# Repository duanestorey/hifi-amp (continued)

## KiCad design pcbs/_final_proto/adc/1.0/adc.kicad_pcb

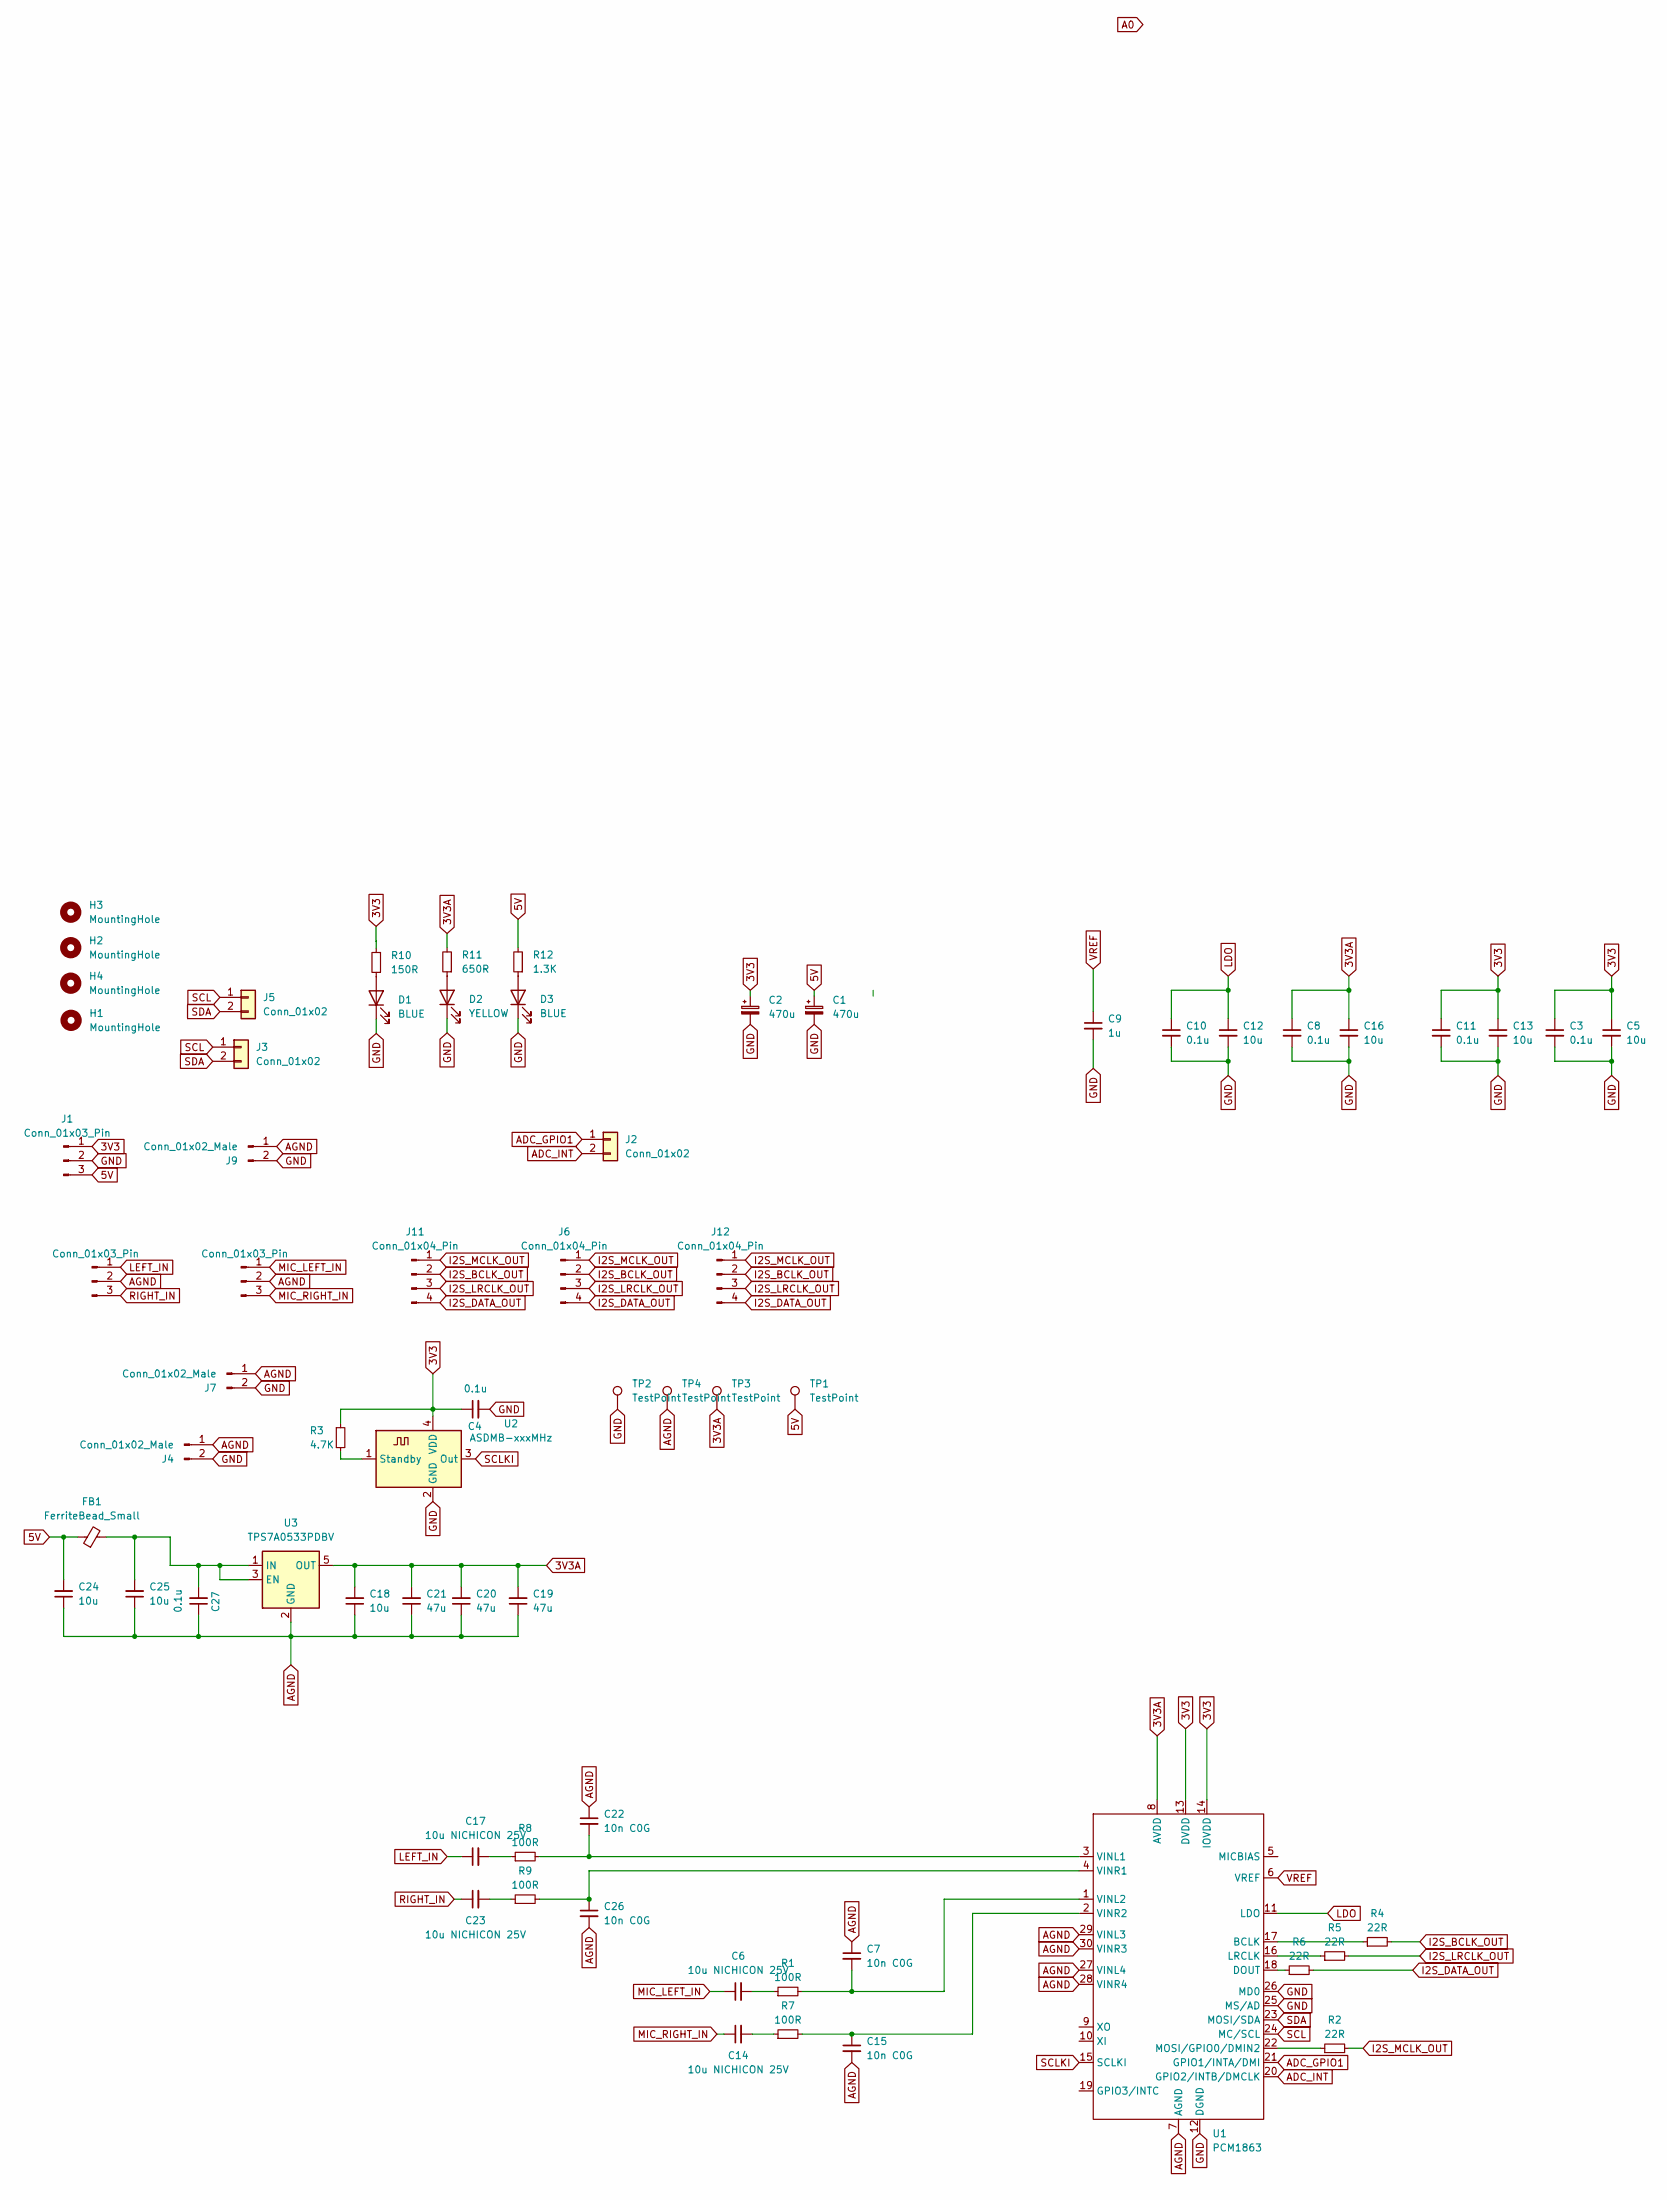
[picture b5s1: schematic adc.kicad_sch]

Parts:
C1, C2: 470u; CP_Radial_D6.3mm_P2.50mm
C3, C8, C10, C11: 0.1u; C_0805_2012Metric_Pad1.18x1.45mm_HandSolder
C4, C27: 0.1u; C_0805_2012Metric_Pad1.18x1.45mm_HandSolder; Mouser 791-0805N103G250CT
C5, C12, C13, C16, C18, C24, C25: 10u; C_1206_3216Metric_Pad1.33x1.80mm_HandSolder
C6, C14, C17, C23: 10u NICHICON 25V; CP_Radial_D5.0mm_P2.00mm
C7, C15, C22, C26: 10n C0G; C_0805_2012Metric_Pad1.18x1.45mm_HandSolder; Mouser 791-0805N103G250CT
C9: 1u; C_1206_3216Metric_Pad1.33x1.80mm_HandSolder
C19, C20, C21: 47u; C_1206_3216Metric_Pad1.33x1.80mm_HandSolder
D1, D3: BLUE; LED_0603_1608Metric
D2: YELLOW; LED_0603_1608Metric
FB1: FerriteBead_Small; R_0603_1608Metric_Pad0.98x0.95mm_HandSolder
H1, H2, H3, H4: MountingHole; MountingHole_3.2mm_M3_DIN965_Pad_TopOnly
J1, J8, J10: Conn_01x03_Pin; JST_PH_B3B-PH-K_1x03_P2.00mm_Vertical
J2, J3, J5: Conn_01x02; JST_PH_B2B-PH-K_1x02_P2.00mm_Vertical
J4, J7, J9: Conn_01x02_Male; PinHeader_1x02_P2.54mm_Vertical
J6, J11: Conn_01x04_Pin; JST_PH_B4B-PH-K_1x04_P2.00mm_Vertical
J12: Conn_01x04_Pin; PinHeader_1x04_P2.54mm_Vertical
R1, R7, R8, R9: 100R; R_0805_2012Metric_Pad1.20x1.40mm_HandSolder; Mouser 603-RT0805FRE13100RL
R2, R4, R5, R6: 22R; R_0805_2012Metric_Pad1.20x1.40mm_HandSolder; Mouser 603-RT0805FRE0722RL
R3: 4.7K; R_0603_1608Metric_Pad0.98x0.95mm_HandSolder; Mouser 603-RT0805FRE0722RL
R10: 150R; R_0603_1608Metric_Pad0.98x0.95mm_HandSolder
R11: 650R; R_0603_1608Metric_Pad0.98x0.95mm_HandSolder
R12: 1.3K; R_0603_1608Metric_Pad0.98x0.95mm_HandSolder
TP1, TP2, TP3, TP4: TestPoint; TestPoint_THTPad_2.5x2.5mm_Drill1.2mm
U1: PCM1863; TSSOP-30_4.4x7.8mm_P0.5mm; Mouser 595-PCM1863DBT
U2: ASDMB-xxxMHz; Oscillator_SMD_Abracon_ASE-4Pin_3.2x2.5mm; Mouser 346-3225Z24.5760C1KX
U3: TPS7A0533PDBV; SOT-23-5

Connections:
3V3: C2.1, C3.1, C4.1, C5.1, C11.1, C13.1, J1.1, R3.1, R10.2, U1.13 (DVDD), U1.14 (IOVDD), U2.4 (VDD)
3V3A: C8.1, C16.1, C18.2, C19.2, C20.2, C21.2, R11.2, TP3.1, U1.8 (AVDD), U3.5 (OUT)
5V: C1.1, C24.2, FB1.1, J1.3, R12.2, TP1.1
ADC_GPIO1: J2.1, U1.21 (GPIO1/INTA/DMI)
ADC_INT: J2.2, U1.20 (GPIO2/INTB/DMCLK)
AGND: C7.1, C15.2, C18.1, C19.1, C20.1, C21.1, C22.1, C24.1, C25.1, C26.2, C27.1, J4.1, J7.1, J8.2, J9.1, J10.2, TP4.1, U1.7 (AGND), U1.27 (VINL4), U1.28 (VINR4), U1.29 (VINL3), U1.30 (VINR3), U3.2 (GND)
GND: C1.2, C2.2, C3.2, C4.2, C5.2, C8.2, C9.2, C10.2, C11.2, C12.2, C13.2, C16.2, D1.1 (K), D2.1 (K), D3.1 (K), J1.2, J4.2, J7.2, J9.2, TP2.1, U1.12 (DGND), U1.25 (MS/AD), U1.26 (MD0), U2.2 (GND)
I2S_BCLK_OUT: J6.2, J11.2, J12.2, R4.2
I2S_DATA_OUT: J6.4, J11.4, J12.4, R6.2
I2S_LRCLK_OUT: J6.3, J11.3, J12.3, R5.2
I2S_MCLK_OUT: J6.1, J11.1, J12.1, R2.2
LDO: C10.1, C12.1, U1.11 (LDO)
LEFT_IN: C17.1, J10.1
MIC_LEFT_IN: C6.1, J8.1
MIC_RIGHT_IN: C14.1, J8.3
unnamed: C6.2, R1.1
unnamed: C14.2, R7.1
unnamed: C17.2, R8.1
unnamed: C23.2, R9.1
unnamed: D1.2 (A), R10.1
unnamed: D2.2 (A), R11.1
unnamed: D3.2 (A), R12.1
unnamed: R4.1, U1.17 (BCLK)
unnamed: R6.1, U1.18 (DOUT)
unnamed: R5.1, U1.16 (LRCLK)
unnamed: R2.1, U1.22 (MOSI/GPIO0/DMIN2)
unnamed: C22.2, R8.2, U1.3 (VINL1)
unnamed: C7.2, R1.2, U1.1 (VINL2)
unnamed: C26.1, R9.2, U1.4 (VINR1)
unnamed: C15.1, R7.2, U1.2 (VINR2)
unnamed: R3.2, U2.1 (Standby)
unnamed: C25.2, C27.2, FB1.2, U3.1 (IN), U3.3 (EN)
RIGHT_IN: C23.1, J10.3
SCL: J3.1, J5.1, U1.24 (MC/SCL)
SCLKI: U1.15 (SCLKI), U2.3 (Out)
SDA: J3.2, J5.2, U1.23 (MOSI/SDA)
VREF: C9.1, U1.6 (VREF)

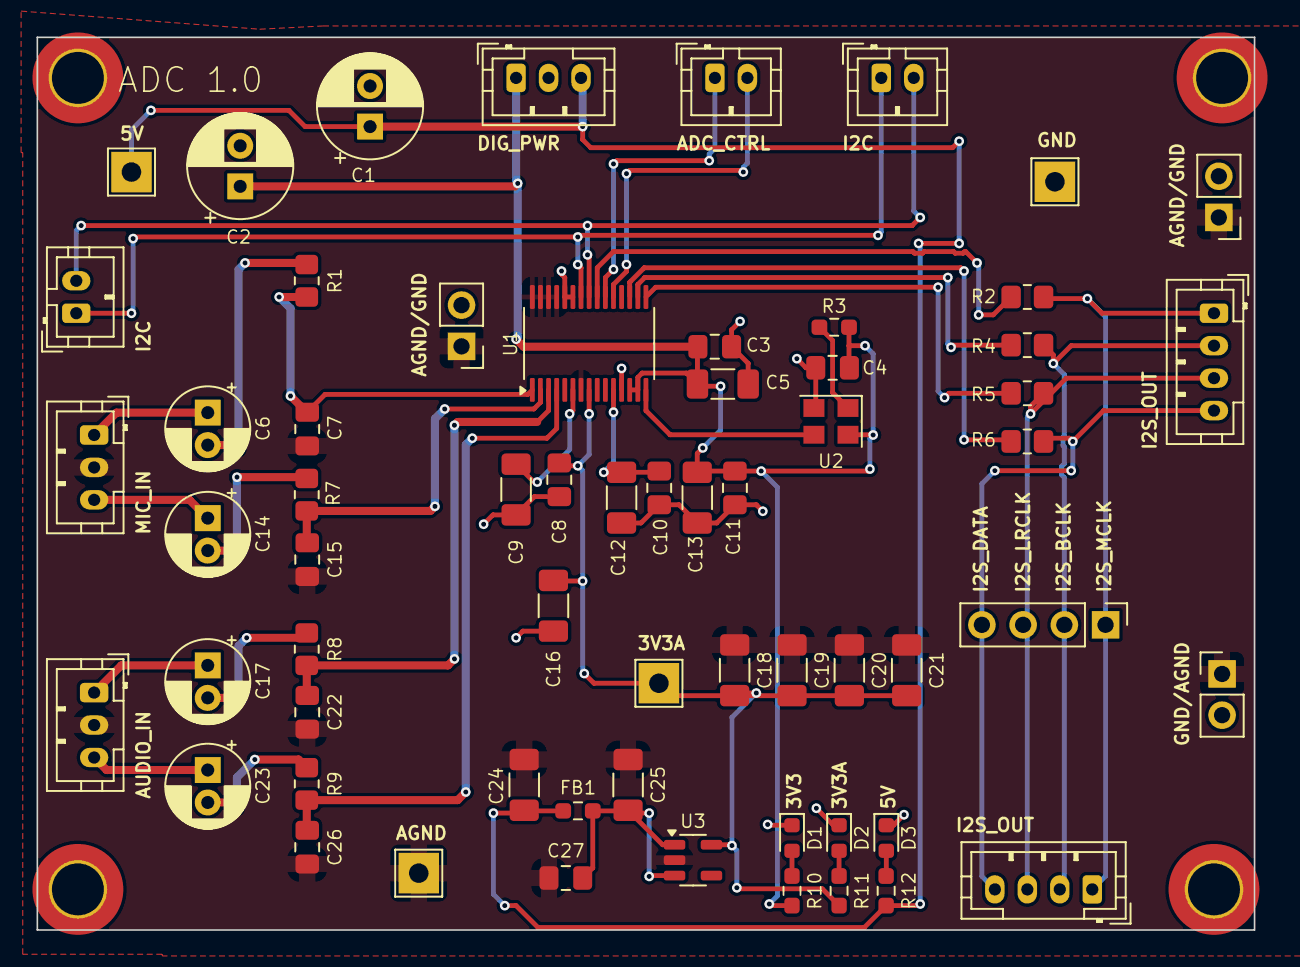
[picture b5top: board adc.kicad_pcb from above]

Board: 2 copper layers, 75.0 x 55.0 mm, 66 parts (0 on the bottom side), 37 nets.

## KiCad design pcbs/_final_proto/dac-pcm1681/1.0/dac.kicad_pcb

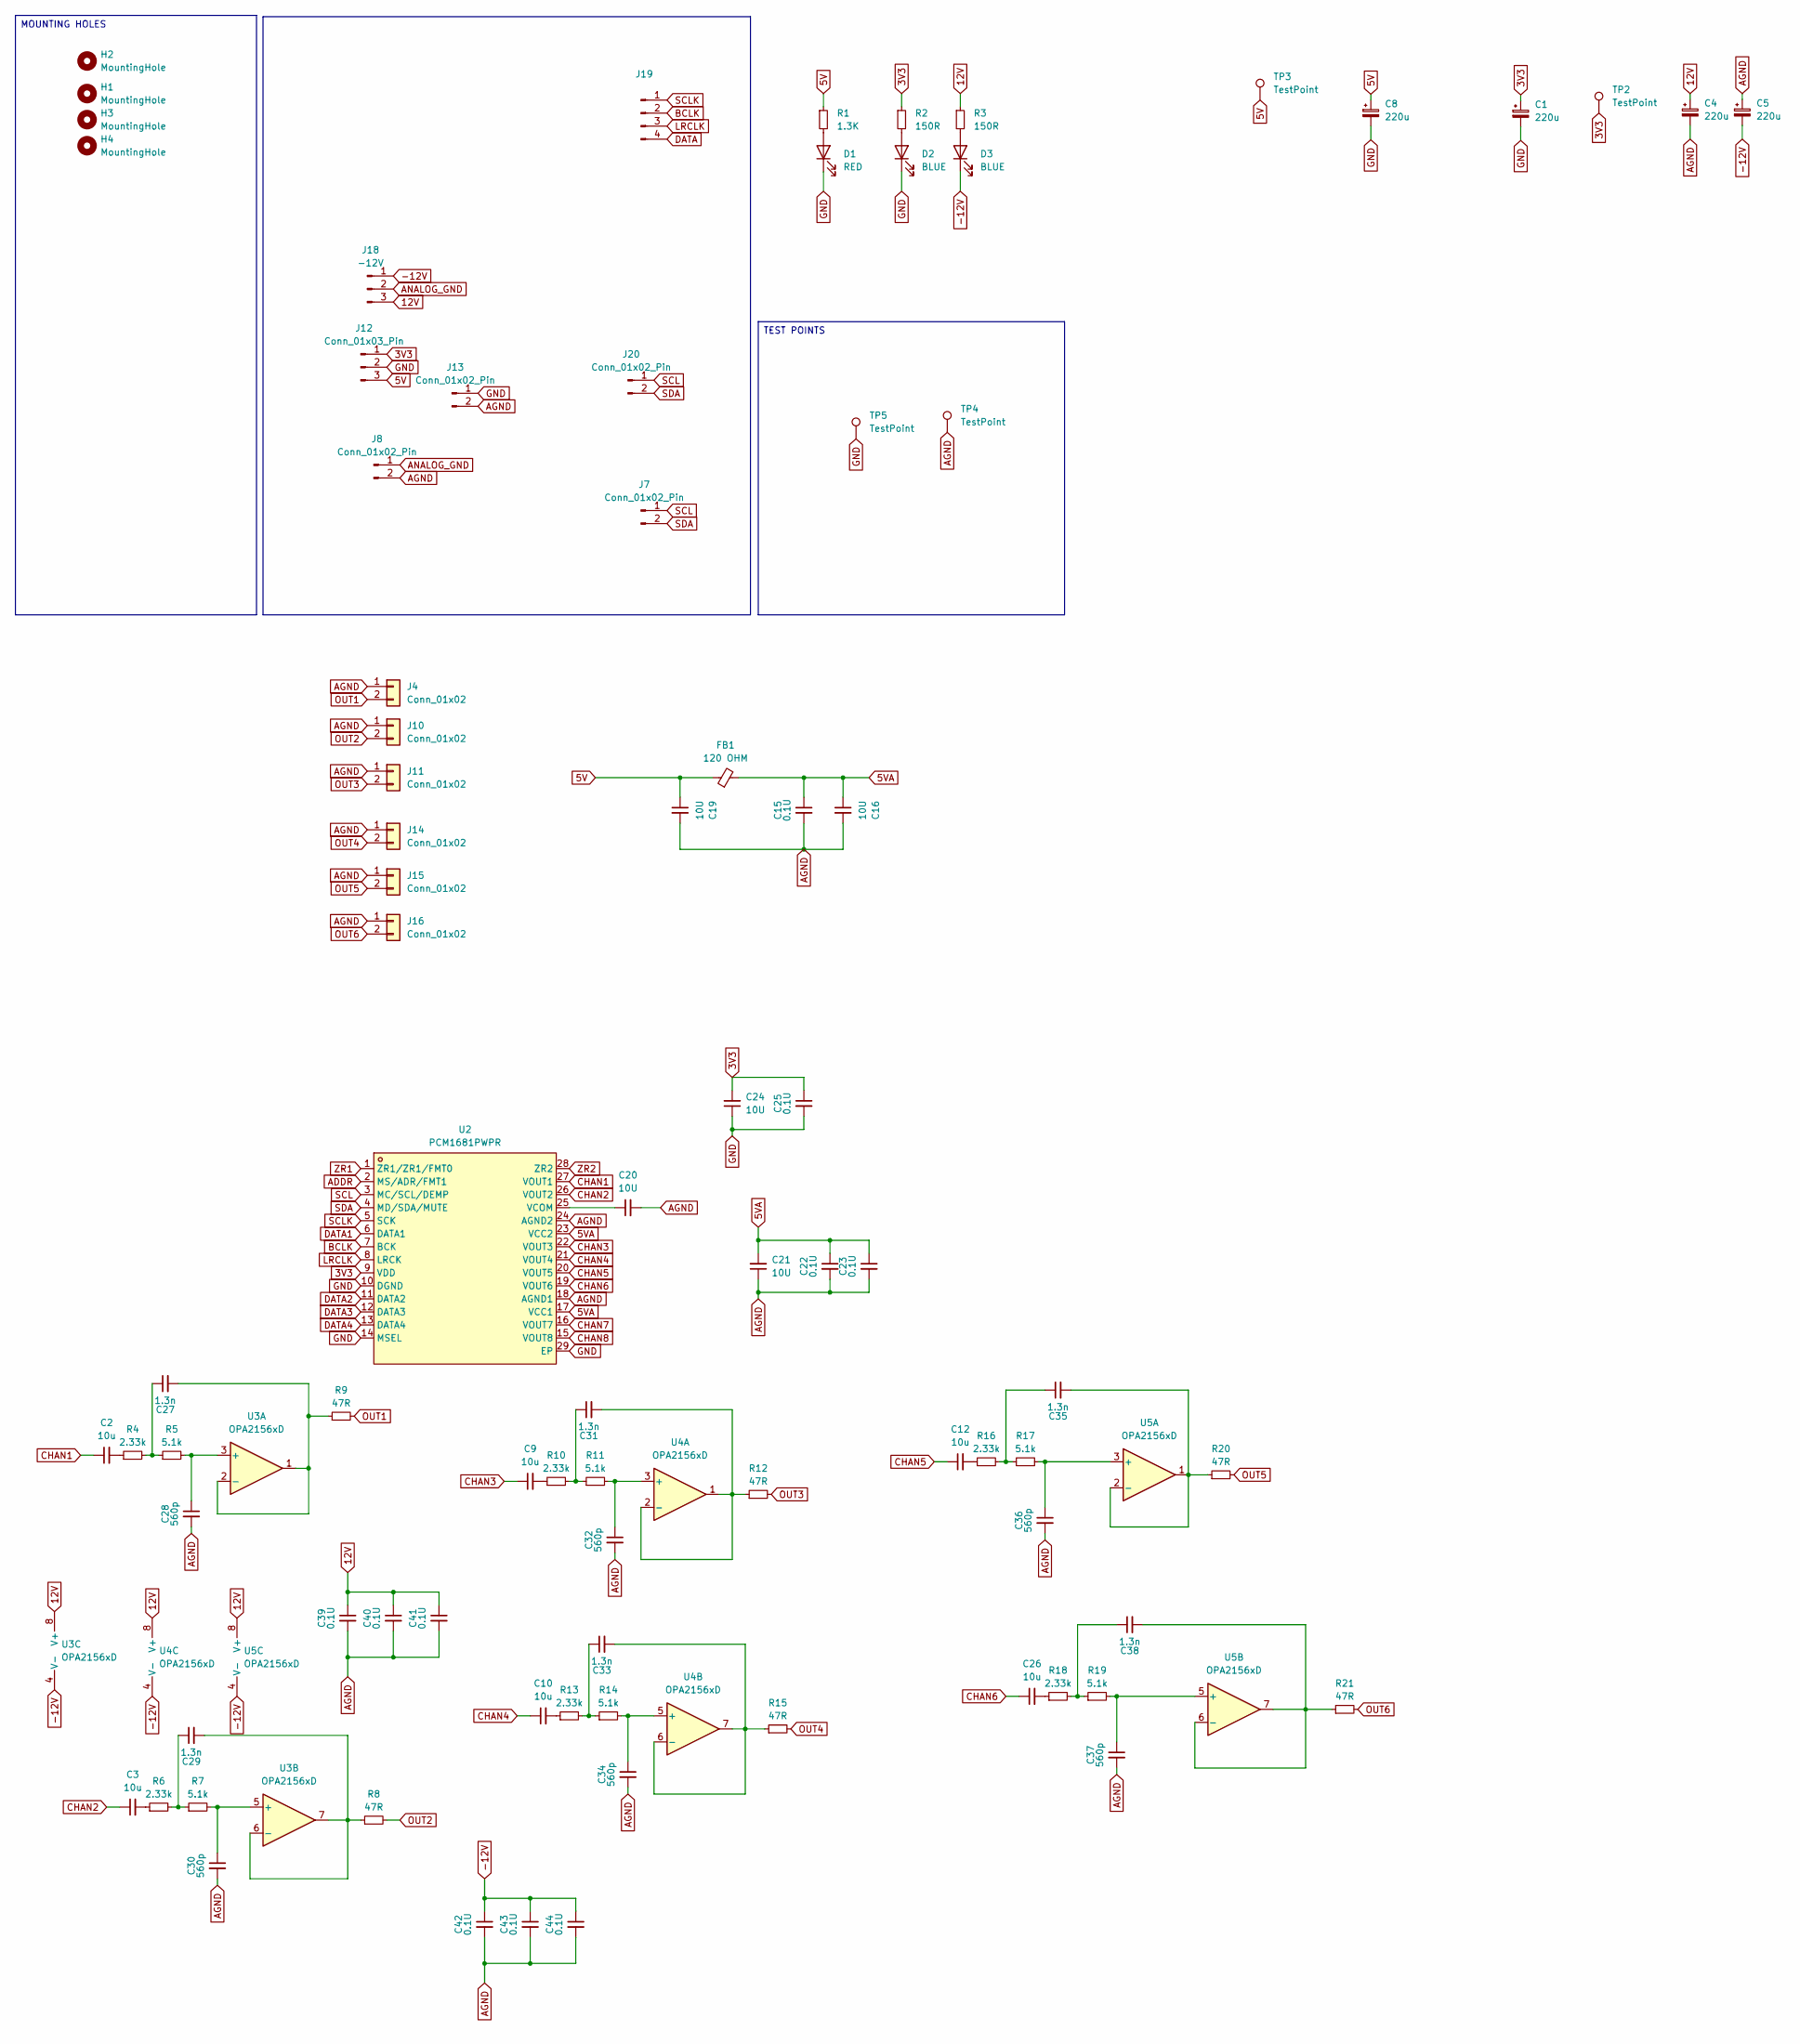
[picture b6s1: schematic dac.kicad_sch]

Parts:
C1, C4, C5, C8: 220u; CP_Radial_D6.3mm_P2.50mm
C2, C3, C9, C10, C12, C26: 10u; C_Radial_D6.3mm_H5.0mm_P2.50mm
C15, C22, C23, C25, C39, C40, C41, C42, C43, C44: 0.1U; C_0805_2012Metric_Pad1.18x1.45mm_HandSolder
C16, C19, C20, C21, C24: 10U; C_1206_3216Metric_Pad1.33x1.80mm_HandSolder
C27, C29, C31, C33, C35, C38: 1.3n; C_0805_2012Metric_Pad1.18x1.45mm_HandSolder
C28, C30, C32, C34, C36, C37: 560p; C_0805_2012Metric_Pad1.18x1.45mm_HandSolder
D1: RED; LED_0805_2012Metric_Pad1.15x1.40mm_HandSolder
D2, D3: BLUE; LED_0805_2012Metric_Pad1.15x1.40mm_HandSolder
FB1: 120 OHM; R_0603_1608Metric_Pad0.98x0.95mm_HandSolder
H1, H2, H3, H4: MountingHole; MountingHole_3.2mm_M3_DIN965_Pad_TopOnly
J4, J10, J11, J14, J15, J16: Conn_01x02; TerminalBlock_Phoenix_PT-1,5-2-3.5-H_1x02_P3.50mm_Horizontal
J7, J20: Conn_01x02_Pin; JST_PH_B2B-PH-K_1x02_P2.00mm_Vertical
J8, J13: Conn_01x02_Pin; PinHeader_1x02_P2.54mm_Vertical
J12: Conn_01x03_Pin; JST_PH_B3B-PH-K_1x03_P2.00mm_Vertical
J18: -12V; JST_PH_B3B-PH-K_1x03_P2.00mm_Vertical
J19: Conn_01x04_Pin; JST_PH_B4B-PH-K_1x04_P2.00mm_Vertical
R1: 1.3K; R_0805_2012Metric_Pad1.20x1.40mm_HandSolder
R2, R3: 150R; R_0805_2012Metric_Pad1.20x1.40mm_HandSolder
R4, R6, R10, R13, R16, R18: 2.33k; R_0805_2012Metric_Pad1.20x1.40mm_HandSolder
R5, R7, R11, R14, R17, R19: 5.1k; R_0805_2012Metric_Pad1.20x1.40mm_HandSolder
R8, R9, R12, R15, R20, R21: 47R; R_0805_2012Metric_Pad1.20x1.40mm_HandSolder
TP2, TP3, TP4, TP5: TestPoint; TestPoint_THTPad_1.5x1.5mm_Drill0.7mm
U2: PCM1681PWPR; TSSOP-28_L9.7-W4.4-P0.65-LS6.4-BL-EP-3; LCSC Part C181571
U3, U4, U5: OPA2156xD; SOIC-8_3.9x4.9mm_P1.27mm

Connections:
3V3: C1.1, C24.2, C25.1, J12.1, R2.1, TP2.1, U2.9 (VDD)
5V: C8.1, C19.1, FB1.1, J12.3, R1.1, TP3.1
5VA: C15.1, C16.1, C21.2, C22.1, C23.1, FB1.2, U2.17 (VCC1), U2.23 (VCC2)
12V: C4.1, C39.1, C40.1, C41.1, J18.3, R3.1, U3.8 (V+), U4.8 (V+), U5.8 (V+)
-12V: C5.2, C42.1, C43.1, C44.1, D3.1 (K), J18.1, U3.4 (V-), U4.4 (V-), U5.4 (V-)
ADDR: U2.2 (MS/ADR/FMT1)
AGND: C4.2, C5.1, C15.2, C16.2, C19.2, C20.2, C21.1, C22.2, C23.2, C28.2, C30.2, C32.2, C34.2, C36.2, C37.2, C39.2, C40.2, C41.2, C42.2, C43.2, C44.2, J4.1, J8.2, J10.1, J11.1, J13.2, J14.1, J15.1, J16.1, TP4.1, U2.18 (AGND1), U2.24 (AGND2)
ANALOG_GND: J8.1, J18.2
BCLK: J19.2, U2.7 (BCK)
CHAN1: C2.1, U2.27 (VOUT1)
CHAN2: C3.1, U2.26 (VOUT2)
CHAN3: C9.1, U2.22 (VOUT3)
CHAN4: C10.1, U2.21 (VOUT4)
CHAN5: C12.1, U2.20 (VOUT5)
CHAN6: C26.1, U2.19 (VOUT6)
CHAN7: U2.16 (VOUT7)
CHAN8: U2.15 (VOUT8)
DATA: J19.4
DATA1: U2.6 (DATA1)
DATA2: U2.11 (DATA2)
DATA3: U2.12 (DATA3)
DATA4: U2.13 (DATA4)
GND: C1.2, C8.2, C24.1, C25.2, D1.1 (K), D2.1 (K), J12.2, J13.1, TP5.1, U2.10 (DGND), U2.14 (MSEL), U2.29 (EP)
LRCLK: J19.3, U2.8 (LRCK)
unnamed: C2.2, R4.1
unnamed: C3.2, R6.1
unnamed: C9.2, R10.1
unnamed: C10.2, R13.1
unnamed: C12.2, R16.1
unnamed: C26.2, R18.1
unnamed: C27.1, R4.2, R5.1
unnamed: C29.1, R6.2, R7.1
unnamed: C31.1, R10.2, R11.1
unnamed: C33.1, R13.2, R14.1
unnamed: C35.1, R16.2, R17.1
unnamed: C38.1, R18.2, R19.1
unnamed: D1.2 (A), R1.2
unnamed: D2.2 (A), R2.2
unnamed: D3.2 (A), R3.2
unnamed: C20.1, U2.25 (VCOM)
unnamed: C28.1, R5.2, U3.3 (+)
unnamed: C27.2, R9.1, U3.1, U3.2 (-)
unnamed: C30.1, R7.2, U3.5 (+)
unnamed: C29.2, R8.1, U3.6 (-), U3.7
unnamed: C32.1, R11.2, U4.3 (+)
unnamed: C31.2, R12.1, U4.1, U4.2 (-)
unnamed: C34.1, R14.2, U4.5 (+)
unnamed: C33.2, R15.1, U4.6 (-), U4.7
unnamed: C36.1, R17.2, U5.3 (+)
unnamed: C35.2, R20.1, U5.1, U5.2 (-)
unnamed: C37.1, R19.2, U5.5 (+)
unnamed: C38.2, R21.1, U5.6 (-), U5.7
OUT1: J4.2, R9.2
OUT2: J10.2, R8.2
OUT3: J11.2, R12.2
OUT4: J14.2, R15.2
OUT5: J15.2, R20.2
OUT6: J16.2, R21.2
SCL: J7.1, J20.1, U2.3 (MC/SCL/DEMP)
SCLK: J19.1, U2.5 (SCK)
SDA: J7.2, J20.2, U2.4 (MD/SDA/MUTE)
ZR1: U2.1 (ZR1/ZR1/FMT0)
ZR2: U2.28 (ZR2)

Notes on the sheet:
MOUNTING HOLES
TEST POINTS

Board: 2 copper layers, 87 parts (0 on the bottom side), 53 nets, no tracks yet.

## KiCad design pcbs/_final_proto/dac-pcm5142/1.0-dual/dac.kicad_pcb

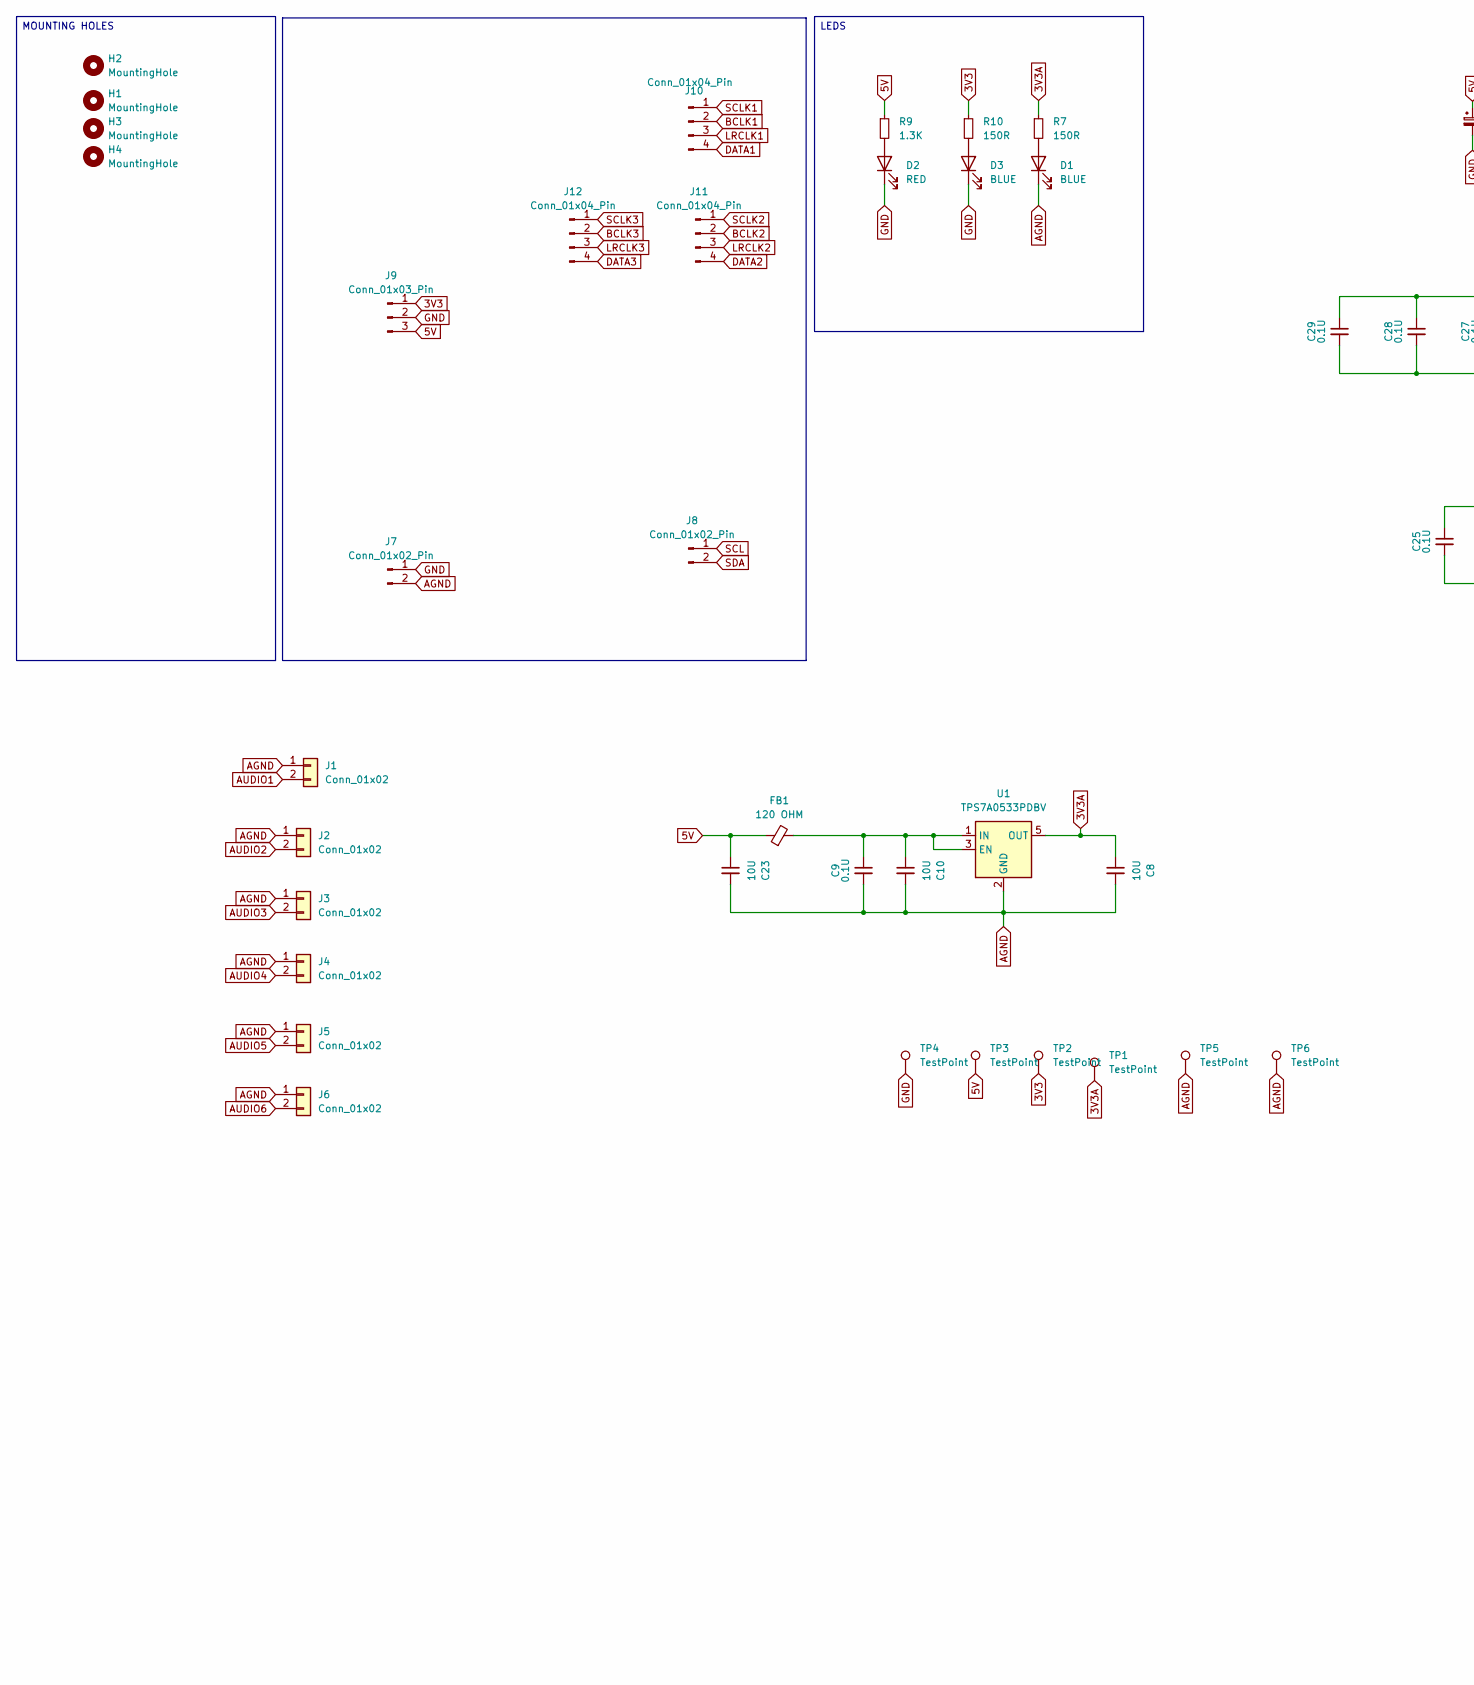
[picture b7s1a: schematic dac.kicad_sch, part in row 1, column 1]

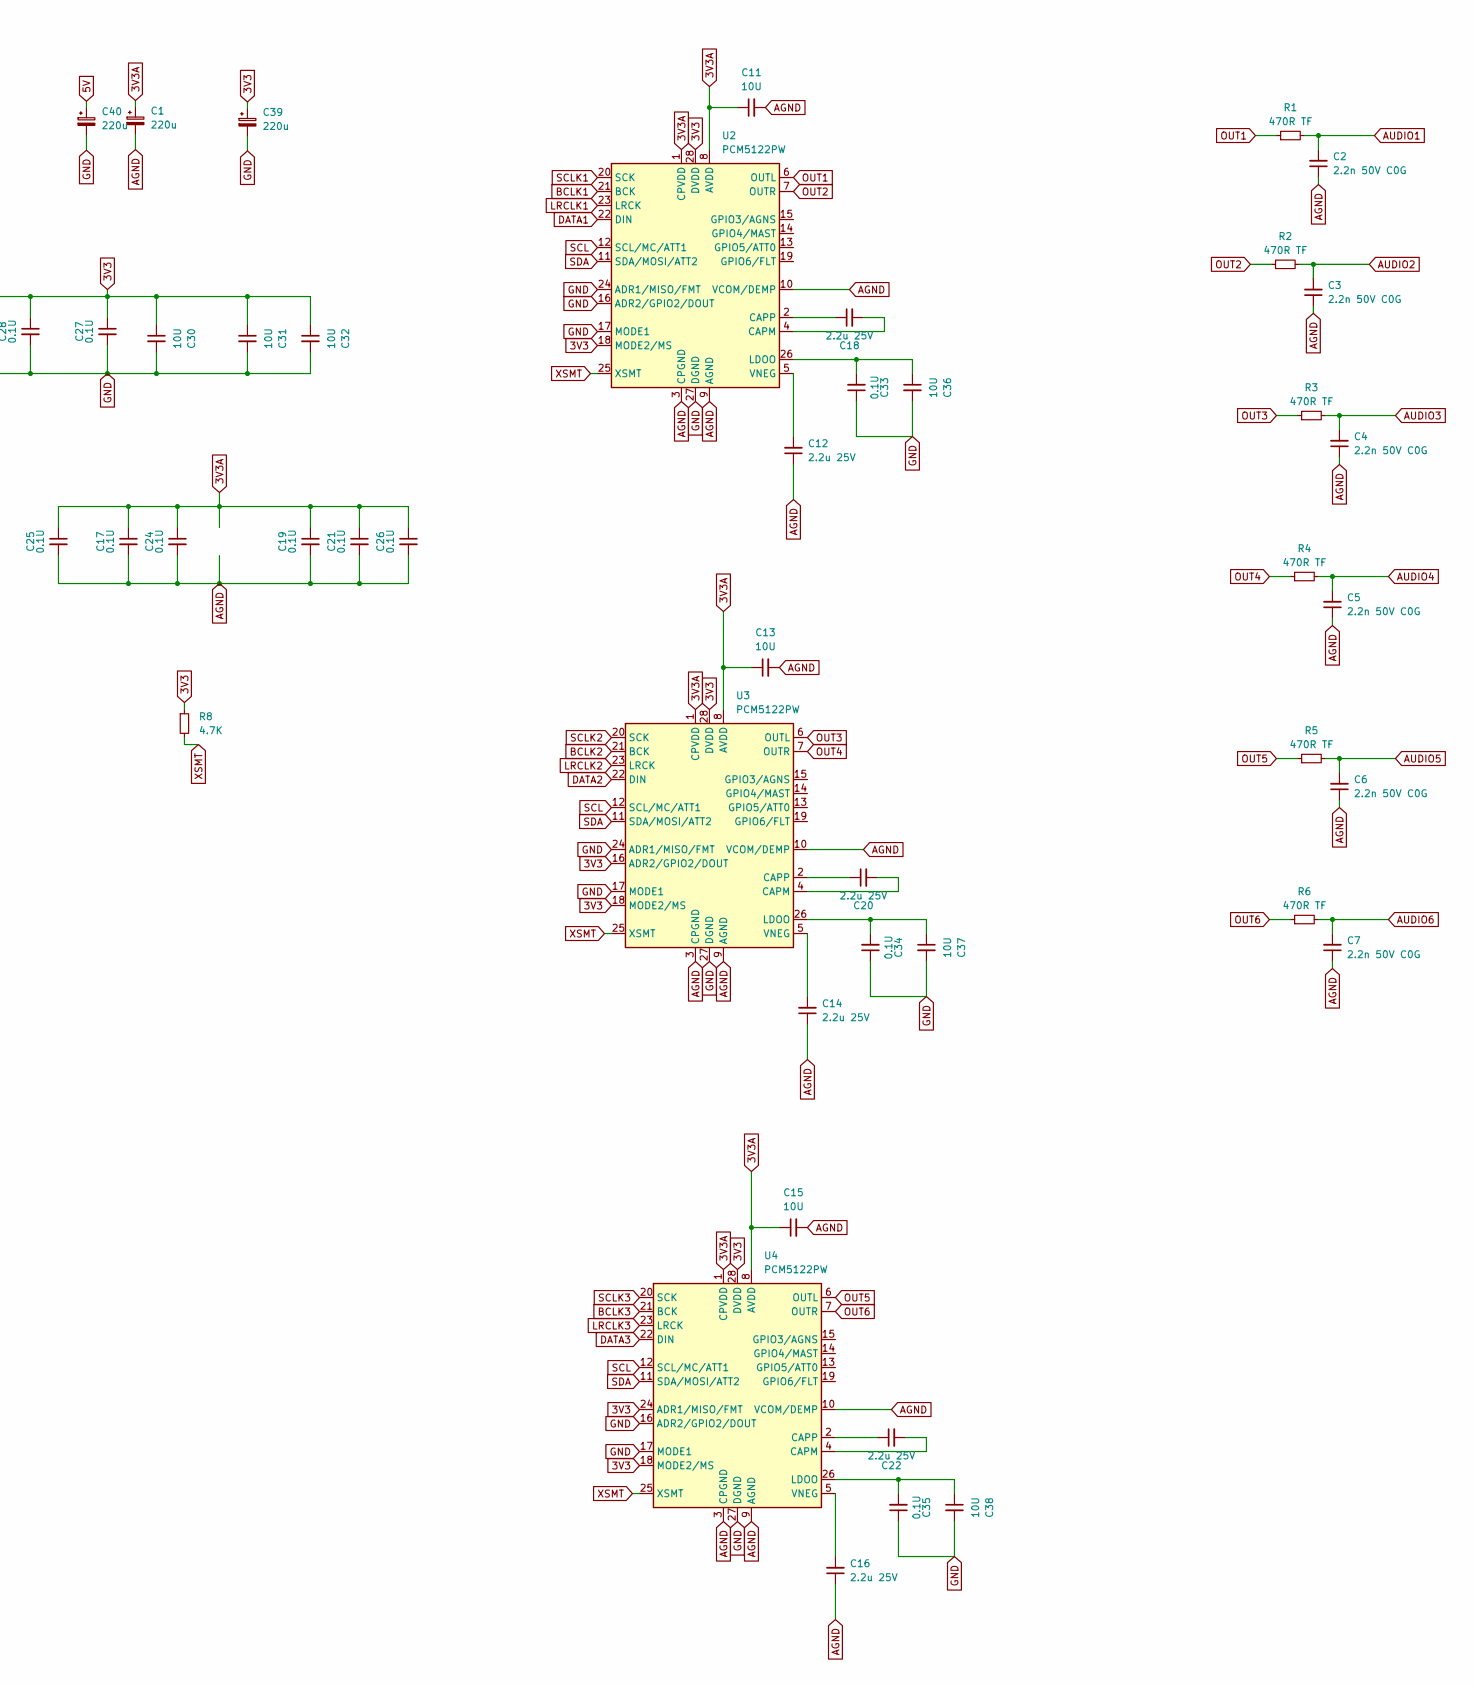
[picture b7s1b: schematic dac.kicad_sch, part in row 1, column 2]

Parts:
C1, C39, C40: 220u; CP_Elec_6.3x7.7
C2, C3, C4, C5, C6, C7: 2.2n 50V C0G; C_0805_2012Metric_Pad1.18x1.45mm_HandSolder; Mouser 791-0805N222G500CT
C8, C10, C11, C13, C15, C23, C30, C31, C32, C36, C37, C38: 10U; C_1206_3216Metric_Pad1.33x1.80mm_HandSolder
C9, C17, C19, C21, C24, C25, C26, C27, C28, C29, C33, C34, C35: 0.1U; C_0805_2012Metric_Pad1.18x1.45mm_HandSolder
C12, C14, C16, C18, C20, C22: 2.2u 25V; C_1206_3216Metric_Pad1.33x1.80mm_HandSolder; Mouser 603-CC1206JKX78BB225
D1, D3: BLUE; LED_0805_2012Metric_Pad1.15x1.40mm_HandSolder
D2: RED; LED_0805_2012Metric_Pad1.15x1.40mm_HandSolder
FB1: 120 OHM; R_0603_1608Metric_Pad0.98x0.95mm_HandSolder
H1, H2, H3, H4: MountingHole; MountingHole_3.2mm_M3_DIN965_Pad_TopOnly
J1, J2, J3, J4, J5, J6: Conn_01x02; TerminalBlock_Phoenix_PT-1,5-2-3.5-H_1x02_P3.50mm_Horizontal
J7: Conn_01x02_Pin; PinHeader_1x02_P2.54mm_Vertical
J8: Conn_01x02_Pin; JST_PH_B2B-PH-K_1x02_P2.00mm_Vertical
J9: Conn_01x03_Pin; JST_PH_B3B-PH-K_1x03_P2.00mm_Vertical
J10, J11, J12: Conn_01x04_Pin; JST_PH_B4B-PH-K_1x04_P2.00mm_Vertical
R1, R2, R3, R4, R5, R6: 470R TF; R_0805_2012Metric_Pad1.20x1.40mm_HandSolder; Mouser 603-RT0805FRE07470RL
R7, R10: 150R; R_0805_2012Metric_Pad1.20x1.40mm_HandSolder
R8: 4.7K; R_0805_2012Metric_Pad1.20x1.40mm_HandSolder
R9: 1.3K; R_0805_2012Metric_Pad1.20x1.40mm_HandSolder
TP1, TP2, TP3, TP4, TP5, TP6: TestPoint; TestPoint_THTPad_1.5x1.5mm_Drill0.7mm
U1: TPS7A0533PDBV; SOT-23-5
U2, U3, U4: PCM5122PW; TSSOP-28_4.4x9.7mm_P0.65mm; Mouser 595-PCM5122PWR

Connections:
3V3: C27.1, C28.1, C29.1, C30.1, C31.1, C32.1, C39.1, J9.1, R8.1, R10.1, TP2.1, U2.18 (MODE2/MS), U2.28 (DVDD), U3.16 (ADR2/GPIO2/DOUT), U3.18 (MODE2/MS), U3.28 (DVDD), U4.18 (MODE2/MS), U4.24 (ADR1/MISO/FMT), U4.28 (DVDD)
3V3A: C1.1, C8.1, C11.1, C13.1, C15.1, C17.1, C19.1, C21.1, C24.1, C25.1, C26.1, R7.1, TP1.1, U1.5 (OUT), U2.1 (CPVDD), U2.8 (AVDD), U3.1 (CPVDD), U3.8 (AVDD), U4.1 (CPVDD), U4.8 (AVDD)
5V: C23.1, C40.1, FB1.1, J9.3, R9.1, TP3.1
AGND: C1.2, C2.1, C3.1, C4.1, C5.1, C6.1, C7.1, C8.2, C9.2, C10.2, C11.2, C12.1, C13.2, C14.1, C15.2, C16.1, C17.2, C19.2, C21.2, C23.2, C24.2, C25.2, C26.2, D1.1 (K), J1.1, J2.1, J3.1, J4.1, J5.1, J6.1, J7.2, TP5.1, TP6.1, U1.2 (GND), U2.3 (CPGND), U2.9 (AGND), U2.10 (VCOM/DEMP), U3.3 (CPGND), U3.9 (AGND), U3.10 (VCOM/DEMP), U4.3 (CPGND), U4.9 (AGND), U4.10 (VCOM/DEMP)
AUDIO1: C2.2, J1.2, R1.2
AUDIO2: C3.2, J2.2, R2.2
AUDIO3: C4.2, J3.2, R3.2
AUDIO4: C5.2, J4.2, R4.2
AUDIO5: C6.2, J5.2, R5.2
AUDIO6: C7.2, J6.2, R6.2
BCLK1: J10.2, U2.21 (BCK)
BCLK2: J11.2, U3.21 (BCK)
BCLK3: J12.2, U4.21 (BCK)
DATA1: J10.4, U2.22 (DIN)
DATA2: J11.4, U3.22 (DIN)
DATA3: J12.4, U4.22 (DIN)
GND: C27.2, C28.2, C29.2, C30.2, C31.2, C32.2, C33.1, C34.1, C35.1, C36.2, C37.2, C38.2, C39.2, C40.2, D2.1 (K), D3.1 (K), J7.1, J9.2, TP4.1, U2.16 (ADR2/GPIO2/DOUT), U2.17 (MODE1), U2.24 (ADR1/MISO/FMT), U2.27 (DGND), U3.17 (MODE1), U3.24 (ADR1/MISO/FMT), U3.27 (DGND), U4.16 (ADR2/GPIO2/DOUT), U4.17 (MODE1), U4.27 (DGND)
LRCLK1: J10.3, U2.23 (LRCK)
LRCLK2: J11.3, U3.23 (LRCK)
LRCLK3: J12.3, U4.23 (LRCK)
unnamed: D1.2 (A), R7.2
unnamed: D2.2 (A), R9.2
unnamed: D3.2 (A), R10.2
unnamed: C9.1, C10.1, FB1.2, U1.1 (IN), U1.3 (EN)
unnamed: C18.2, U2.4 (CAPM)
unnamed: C18.1, U2.2 (CAPP)
unnamed: C33.2, C36.1, U2.26 (LDOO)
unnamed: C12.2, U2.5 (VNEG)
unnamed: C20.2, U3.4 (CAPM)
unnamed: C20.1, U3.2 (CAPP)
unnamed: C34.2, C37.1, U3.26 (LDOO)
unnamed: C14.2, U3.5 (VNEG)
unnamed: C22.2, U4.4 (CAPM)
unnamed: C22.1, U4.2 (CAPP)
unnamed: C35.2, C38.1, U4.26 (LDOO)
unnamed: C16.2, U4.5 (VNEG)
OUT1: R1.1, U2.6 (OUTL)
OUT2: R2.1, U2.7 (OUTR)
OUT3: R3.1, U3.6 (OUTL)
OUT4: R4.1, U3.7 (OUTR)
OUT5: R5.1, U4.6 (OUTL)
OUT6: R6.1, U4.7 (OUTR)
SCL: J8.1, U2.12 (SCL/MC/ATT1), U3.12 (SCL/MC/ATT1), U4.12 (SCL/MC/ATT1)
SCLK1: J10.1, U2.20 (SCK)
SCLK2: J11.1, U3.20 (SCK)
SCLK3: J12.1, U4.20 (SCK)
SDA: J8.2, U2.11 (SDA/MOSI/ATT2), U3.11 (SDA/MOSI/ATT2), U4.11 (SDA/MOSI/ATT2)
XSMT: R8.2, U2.25 (XSMT), U3.25 (XSMT), U4.25 (XSMT)

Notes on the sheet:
MOUNTING HOLES
LEDS

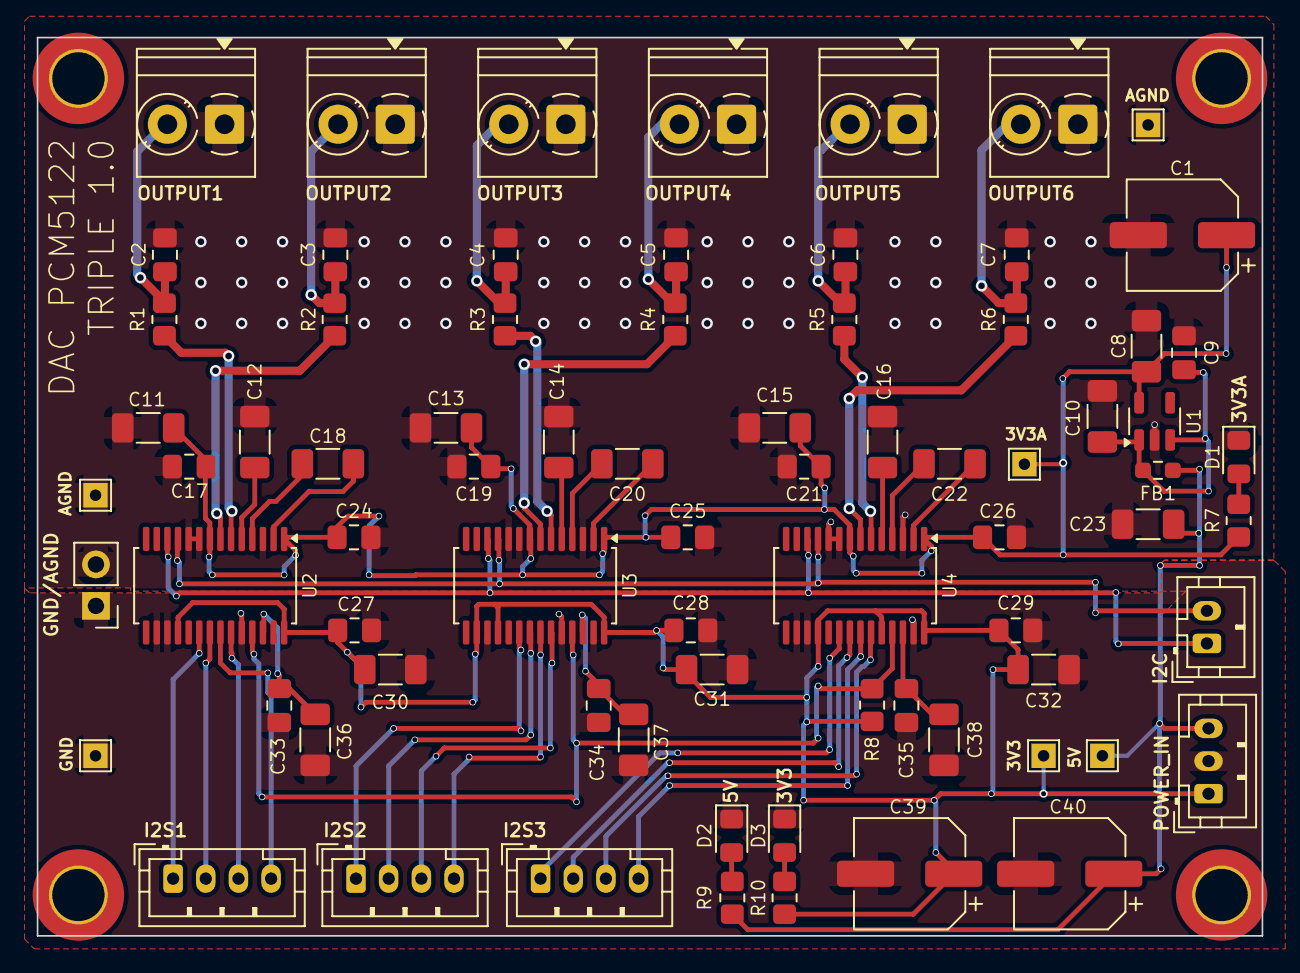
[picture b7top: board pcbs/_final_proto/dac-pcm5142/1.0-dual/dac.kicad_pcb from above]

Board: 2 copper layers, 75.0 x 55.0 mm, 80 parts (0 on the bottom side), 48 nets.
